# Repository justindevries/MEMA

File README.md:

# MEMA Build Files
An open-source, multiplexed potentiostat kit for at-home diagnostic testing, to be used in tandem with a custom microfluidic assay

This repository contains files for the hardware and firmware required to fabricate, assemble, and initialize the potentiostat.

For source code for complementary iOS app, please see [here](https://github.com/juliamstrauss/NFluidEX-iOS).

For source code for complementary Android app, please see [here](https://github.com/juliamstrauss/NFluidEX-Android).

MEMA is based on ABE-Stat, an open-source potentiostat designed by Jenkins et al. in 2019. Their open-source publication can be accessed [here](https://iopscience.iop.org/article/10.1149/2.0061909jes) for extensive documentation on the basis of its functionality.

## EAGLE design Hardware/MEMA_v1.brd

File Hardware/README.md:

# MEMA Hardware
Design and assembly files for manufacturing of the potentiostat's PCB and 3D-printed housing unit

For Arduino firmware files, please see [here](https://github.com/justindevries/NFluidEX/tree/main/Arduino).

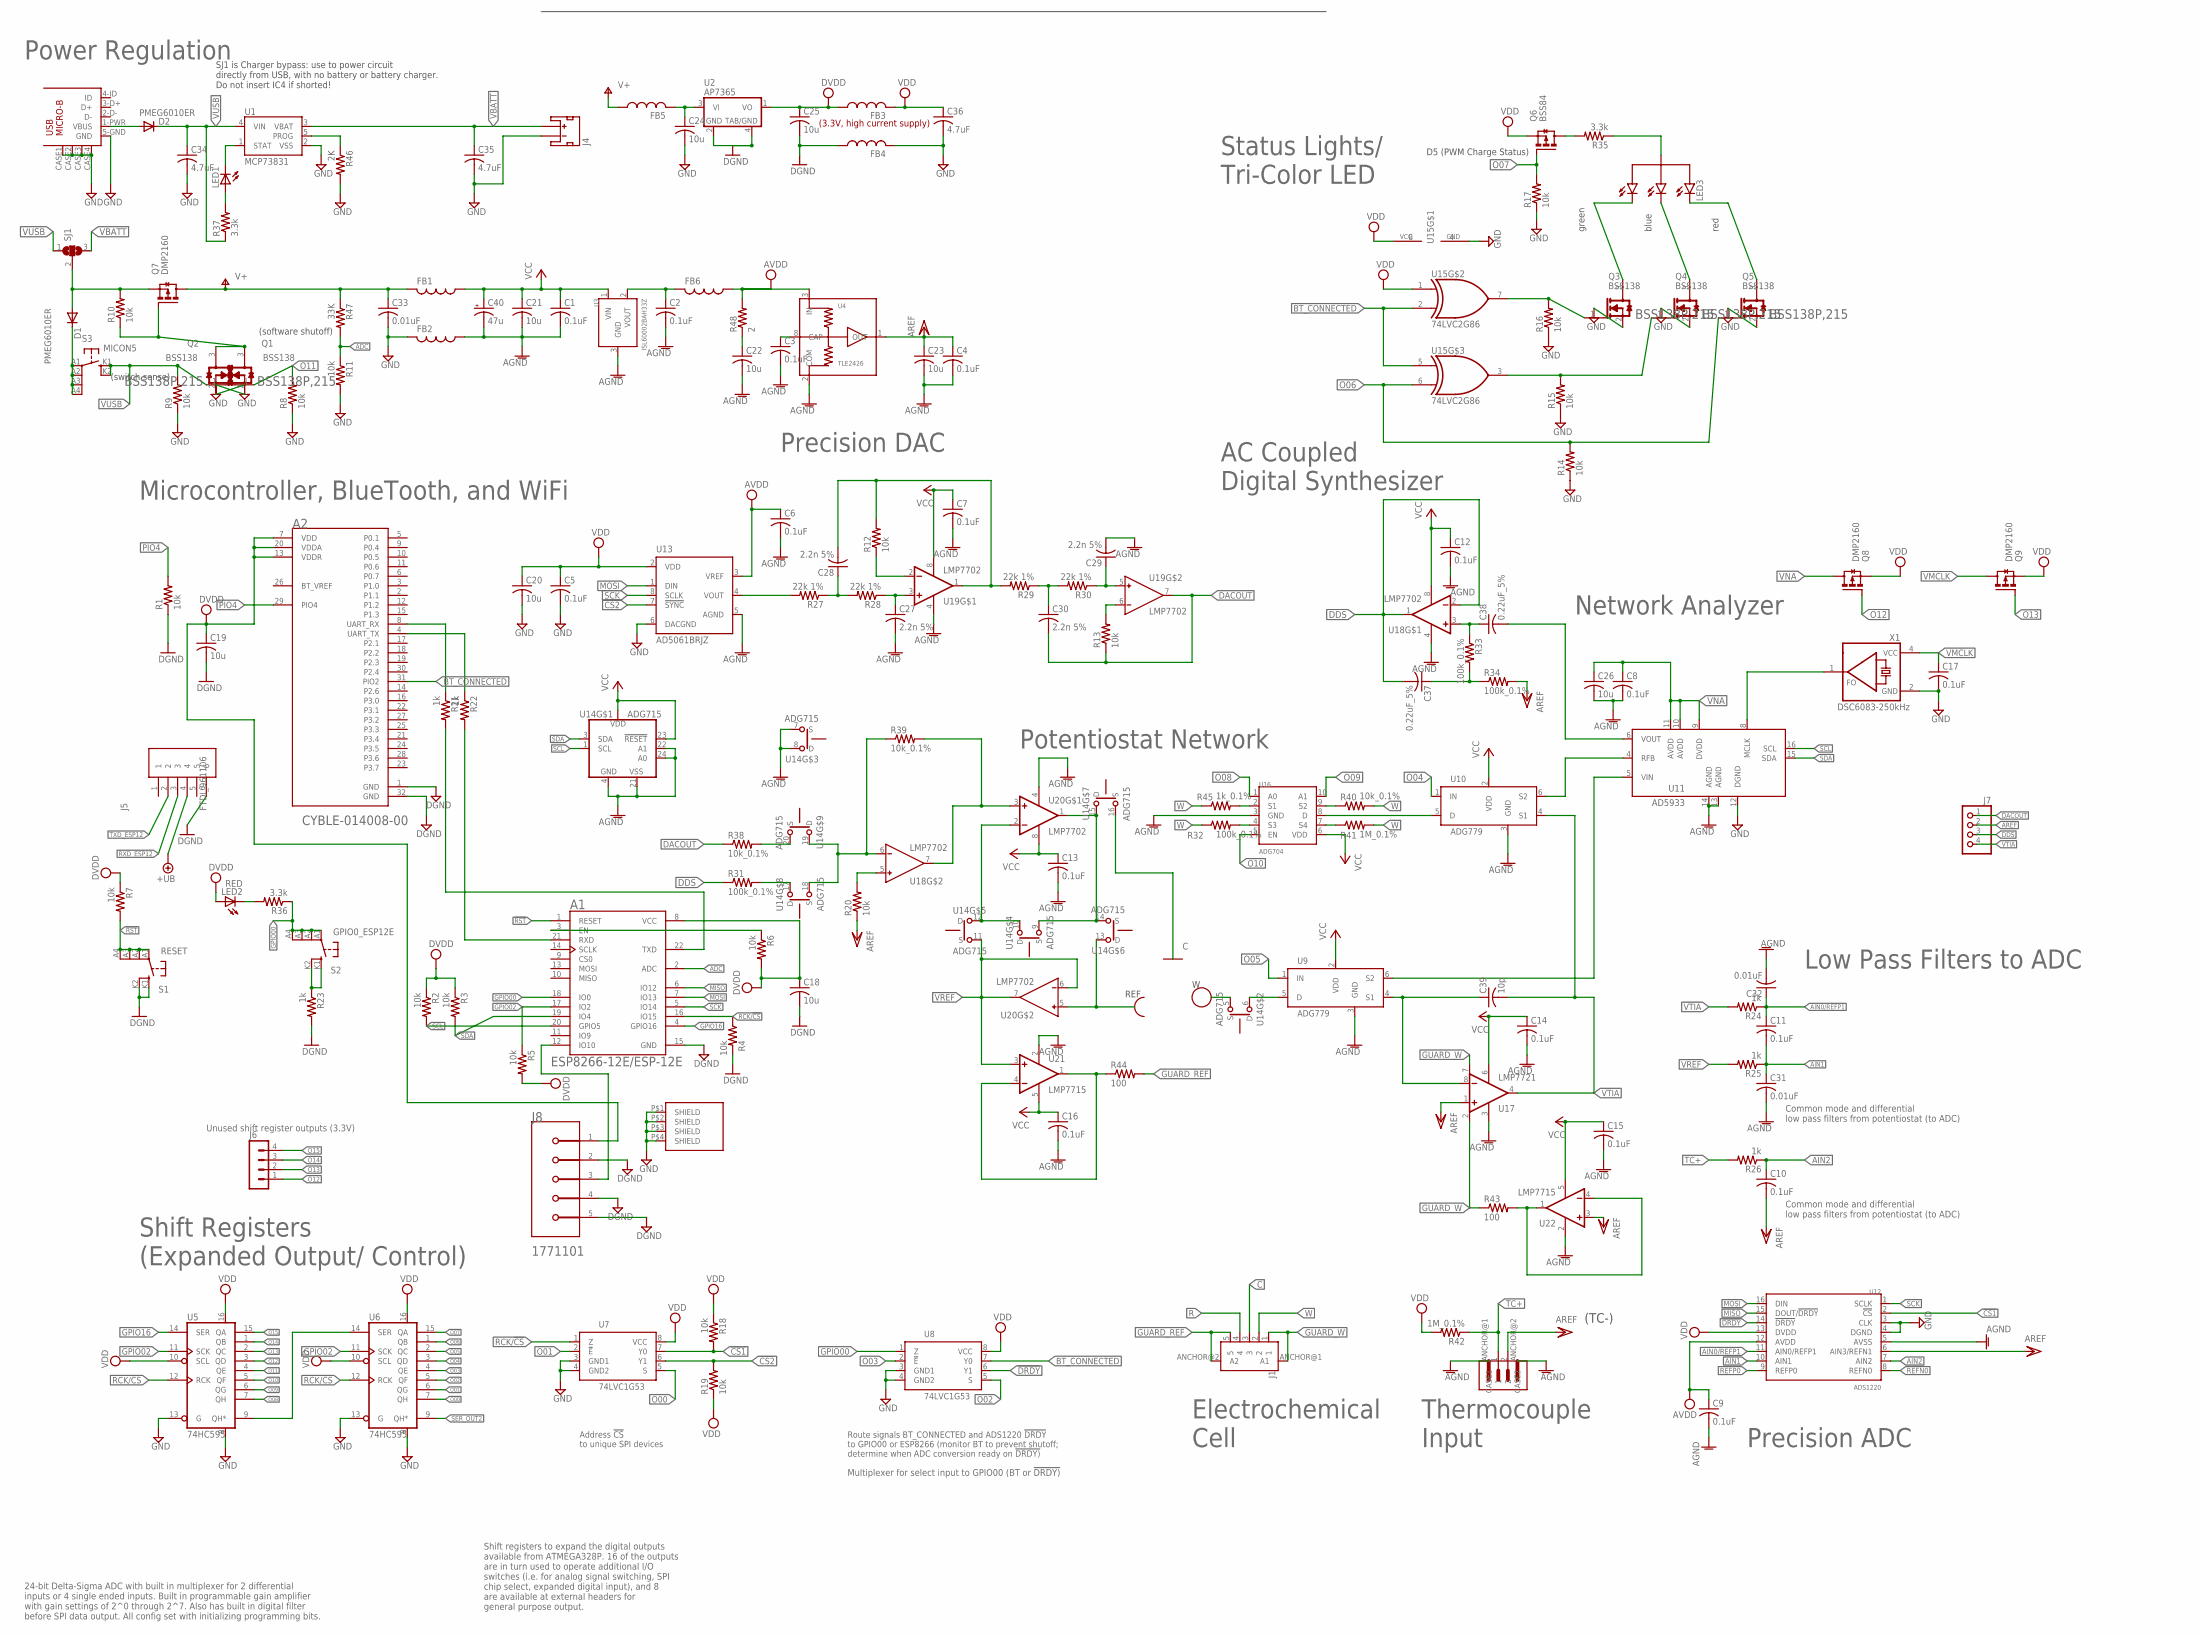
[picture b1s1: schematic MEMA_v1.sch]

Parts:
A1: ESP8266-12E/ESP-12E; XCVR_ESP8266-12E/ESP-12E
A2: CYPRESS_SEMICONDUCTOR_CYBLE-014008-00CYPRESS_SEMI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; CYPRESS_SEMICONDUCTOR_CYBLE-014008-00_0
C1, C2, C3, C4, C5, C6, C7, C8, C9, C10, C11, C12, C13, C14, C15, C16, C17: 0.1uF; C0805
C18, C19, C20, C21, C22, C23, C24, C25, C26: 10u; C0805
C27, C28, C29, C30: 2.2n 5%; C0805
C31, C32, C33: 0.01uF; C0805
C34, C35, C36: 4.7uF; C0805
C37, C38: 0.22uF_5%; C0805
C39: 10p; C0805
C40: 47u; D/7343-31W
D1, D2: PMEG6010ER; DIODE_SOD123
FB1, FB2, FB3, FB4, FB5, FB6: FERRITE_BEAD_5A_0805; R0805
J1: 5-PIN-VERTICAL-PHOENIX_2.5MM-SMD; 5-PIN-VERT_PHOENIX_SMD
J2: 1A_JENKINS_2013_2PIN_SMD_PHOENIX_CONTACTVERTICAL; 2-PIN-VERT_PHOENIX_SMD
J3: USB-MICRO-B; USB_MICRO_B_WURTH_629105136821
J4: JST_2MM_MALE; JST-2-SMD
J5: FTDI_961106; TSM-106-XX-XXX-SV
J6: MA04-1
J7: PINHD-1X4; 1X04
J8: PHOENIX_CONTACT_1771101PHOENIX_CONTACT_1771101_0_0; PHOENIX_CONTACT_1771101_0
LED1: LEDCHIPLED_1206; CHIPLED_1206
LED2: RED; LED-1206
LED3: LED_RBG_COM_ANODE; LED_RGB_WURTH_150141M173100
Q1, Q2, Q3, Q4, Q5: BSS138; NEXPERIA_BSS138P_215_0
Q6: BSS84; SOT-23-3
Q7, Q8, Q9: DMP2160; SOT-23-3
R1, R2, R3, R4, R5, R6, R7, R8, R9, R10, R11, R12, R13, R14, R15, R16, R17, R18, R19, R20: 10k; R0805
R21, R22, R23, R24, R25, R26: 1k; R0805
R27, R28, R29, R30: 22k 1%; R0805
R31, R32, R33, R34: 100k_0.1%; R0805
R35, R36, R37: 3.3k; R0805
R38, R39, R40: 10k_0.1%; R0805
R41, R42: 1M_0.1%; R0805
R43, R44: 100; R0805
R45: 1k_0.1%; R0805
R46: 2K; R0805
R47: 33K; R0805
R48: 2; R2512
S1: RESET; RAFI-MICON5_SWITCH
S2: GPIO0_ESP12E; RAFI-MICON5_SWITCH
S3: MICON5; RAFI-MICON5_SWITCH
SH1: SMARTDART_SHIELD; SMARTDART-SHIELD
SJ1: SJ2W; SJ_2
U1: MCP73831; SOT23-5
U2: AP7365; SOT-223
U3: ISL60002BAH33Z; SOT-23-3
U4: TLE2426; SOIC-8
U5, U6: 74HC595; TSSOP16
U7, U8: 74LVC1G53; VSSOP8
U9, U10: ADG779; SC70-6
U11: AD5933; SSOP-16
U12: ADS1220; TSSOP16
U13: AD5061BRJZ; SOT-23-8
U14: ADG715; TSSOP24
U15: 74LVC2G86; US-8
U16: ADG704; MSOP10
U17: LMP7721; SOIC-8
U18, U19: LMP7702; UMAX8
U20: LMP7702; MSOP8
U21, U22: LMP7715; SOT23-5
X1: DSC6083-250kHz; DSC60XX_OSCILLATOR_3.2X2.5MM

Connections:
!CS1: R18.2, U7.7 (Y0), U12.2 (!CS)
!CS2: R19.2, U7.6 (Y1), U13.7 (!SYNC)
!DRDY: U8.6 (Y1), U12.14 (!DRDY)
!RST: A1.1 (RESET), R7.2, S1.A1, S1.A2 (P1), S1.A3 (P2), S1.A4 (P3)
+UB: J5.4
AD5933_VIN: U9.6 (S2), U11.5 (VIN)
ADC: A1.2 (ADC), R11.1, R47.2
AGND: C1.2, C2.2, C3.2, C4.2, C6.2, C7.2, C8.2, C9.2, C12.2, C13.2, C14.2, C15.2, C16.2, C21.2, C22.2, C23.2, C26.2, C27.2, C29.2, C31.2, C32.2, C40.-, FB2.1, J2.ANCHOR@1 (CASE1), J2.ANCHOR@2 (CASE2), U3.3 (GND), U4.2 (COM), U9.3 (GND), U10.3 (GND), U11.13 (AGND), U11.14 (AGND), U12.5 (AVSS), U13.5 (AGND), U14.4 (GND), U14.7 (S), U14.8 (D), U14.21 (VSS), U14.22 (A1), U14.24 (A0), U16.3 (GND), U17.3 (V-), U18.4 (V-), U19.4 (V-), U20.4 (V-), U21.2 (V-), U22.2 (V-)
AIN0/REFP1: C11.1, C32.1, R24.1, U12.11 (AIN0/REFP1)
AIN1: C11.2, C31.1, R25.1, U12.10 (AIN1)
AIN2: C10.1, R26.1, U12.7 (AIN2)
AREF: C4.1, C10.2, C23.1, J2.2, J7.2, R20.1, R34.2, U4.1 (OUT), U12.6 (AIN3/REFN1), U17.1 (+IN), U22.3 (+IN)
AVDD: C6.1, C9.1, FB6.1, R48.2, U4.3 (IN), U12.12 (AVDD), U13.3 (VREF)
BT_CONNECTED: A2.31 (PIO2), U8.7 (Y0), U15.2 (I1), U15.5 (I0)
BT_VREF: A2.26 (BT_VREF)
C: J1.3, U14.16 (S)
DACOUT: C30.2, J7.1, R13.1, R38.1, U19.7 (OUT)
DDS: C37.2, J7.3, R31.1, U18.1 (OUT), U18.2 (-IN)
DGND: A1.15 (GND), A2.1 (GND), A2.32 (GND), C18.2, C19.2, C25.2, FB4.1, J5.6, J8.2, J8.4 (MNT_1), J8.5 (MNT_2), R1.1, R4.2, R23.2, S1.K1 (S), S1.K2 (S1), U2.2 (GND), U2.4 (GND1)
DVDD: A1.8 (VCC), A2.7 (VDD), A2.13 (VDDR), A2.20 (VDDA), C18.1, C19.1, C25.1, FB3.1, J8.1, LED2.A, R2.1, R3.1, R5.2, R6.2, R7.1, U2.1 (VO)
GND: C5.2, C17.2, C20.2, C24.2, C33.2, C34.2, C35.2, C36.2, FB2.2, FB4.2, J3.5-GND (GND), J3.CASE1 (CASE), J3.CASE2 (CASE), J3.CASE3 (CASE), J3.CASE4 (CASE), J4.1 (-), Q1.2 (S), Q2.2 (S), Q3.2 (S), Q4.2 (S), Q5.2 (S), R8.1, R9.1, R11.2, R14.1, R15.1, R16.1, R17.1, R46.2, SH1.P$1, SH1.P$2, SH1.P$3, SH1.P$4, U1.2 (VSS), U5.8 (GND), U5.13 (G), U6.8 (GND), U6.13 (G), U7.3 (GND1), U7.4 (GND2), U8.3 (GND1), U8.4 (GND2), U11.12 (DGND), U12.3 (CLK), U12.4 (DGND), U13.6 (DACGND), U15.4 (GND), X1.2 (GND)
GPIO00: A1.18 (IO0), R36.1, S2.A1, S2.A2 (P1), S2.A3 (P2), S2.A4 (P3), U8.1 (Z)
GPIO02: A1.17 (IO2), R5.1, U5.11 (SCK), U6.11 (SCK)
GPIO10: A1.12 (IO10), J8.3
GPIO16: A1.4 (GPIO16), U5.14 (SER)
GUARD_REF: J1.5, J1.ANCHOR@2 (A2), R44.2
GUARD_W: J1.1, J1.ANCHOR@1 (A1), R43.1, U17.2 (GUARD), U17.7 (GUARD)
MISO: A1.6 (IO12), U12.15 (DOUT/!DRDY)
MOSI: A1.7 (IO13), U12.16 (DIN), U13.1 (DIN)
unnamed: A2.8 (UART_RX), R21.1
unnamed: U14.10 (D), U14.12 (D), U20.2 (-IN)
unnamed: D2.A, J3.1-PWR (VBUS)
unnamed: A2.4 (UART_TX), R22.1
unnamed: Q3.1 (G), R16.2, U15.7 (O)
unnamed: U9.5 (D), U14.6 (D)
unnamed: R46.1, U1.5 (PROG)
unnamed: U5.9 (QH*), U6.14 (SER)
unnamed: C27.1, R28.1, U19.3 (+IN)
unnamed: LED1.C, U1.1 (STAT)
unnamed: R27.2, U13.4 (VOUT)
unnamed: LED1.A, R37.2
unnamed: C22.1, R48.1
unnamed: R31.2, U14.17 (D)
unnamed: C28.1, R27.1, R28.2
unnamed: R23.1, S2.K1 (S), S2.K2 (S1)
unnamed: Q4.1 (G), R15.2, U15.3 (O)
unnamed: D1.C, S3.A1, S3.A2 (P1), S3.A3 (P2), S3.A4 (P3)
unnamed: C3.1, U4.8 (CAP)
unnamed: C28.2, R12.2, R29.2, U19.1 (OUT)
unnamed: C30.1, R29.1, R30.2
unnamed: C29.1, R30.1, U19.5 (IN+)
unnamed: R12.1, U19.2 (-IN)
unnamed: U14.9 (S), U14.14 (S), U14.15 (D), U20.1 (OUT)
unnamed: R13.2, U19.6 (IN-)
unnamed: LED2.C, R36.2
unnamed: C2.1, FB6.2, U3.2 (VOUT)
unnamed: C39.1, U9.4 (S1), U17.8 (-IN)
unnamed: R39.1, U14.18 (S), U14.19 (D), U18.6 (IN-)
unnamed: R39.2, U18.7 (OUT), U20.3 (+IN)
unnamed: U10.6 (S2), U11.4 (RFB)
unnamed: R41.1, U16.7 (S4)
unnamed: R44.1, U21.1 (OUT), U21.4 (-IN)
unnamed: R40.1, U16.9 (S2)
unnamed: Q1.3 (D), Q2.3 (D), Q7.1 (G), R10.1
unnamed: U10.5 (D), U16.8 (D)
unnamed: R45.2, U16.2 (S1)
unnamed: R32.2, U16.4 (S3)
unnamed: LED3.G, Q3.3 (D)
unnamed: R43.2, U22.1 (OUT), U22.4 (-IN)
unnamed: LED3.B, Q4.3 (D)
unnamed: LED3.R, Q5.3 (D)
unnamed: Q6.3 (D), R35.2
unnamed: LED3.A, R35.1
unnamed: R38.2, U14.20 (S)
unnamed: C24.1, FB5.2, U2.3 (VI)
unnamed: A1.3 (EN), R6.1
unnamed: U11.8 (MCLK), X1.1 (FO)
unnamed: D1.A, Q7.2 (S), R10.2, SJ1.2
unnamed: R20.2, U18.5 (IN+)
unnamed: C37.1, R33.2, R34.1
unnamed: C38.1, R33.1, U18.3 (+IN)
unnamed: C38.2, U11.6 (VOUT)
O00: U6.7 (QH), U7.5 (S)
O01: U6.6 (QG), U7.2 (!E)
O02: U6.5 (QF), U8.5 (S)
O03: U6.4 (QE), U8.2 (!E)
O04: U6.3 (QD), U10.1 (IN)
O05: U6.2 (QC), U9.1 (IN)
O06: Q5.1 (G), R14.2, U6.1 (QB), U15.6 (I1)
O07: Q6.1 (G), R17.2, U6.15 (QA)
O08: U5.7 (QH), U16.1 (A0)
O09: U5.6 (QG), U16.10 (A1)
O10: U5.5 (QF), U16.5 (EN)
O11: Q1.1 (G), R8.2, U5.4 (QE)
O12: J6.1, Q8.1 (G), U5.3 (QD)
O13: J6.2, Q9.1 (G), U5.2 (QC)
O14: J6.3, U5.1 (QB)
O15: J6.4, U5.15 (QA)
PIO4: A2.29 (PIO4), R1.2
R: J1.4, U14.13 (D), U20.5 (IN+)
RCK/!CS: A1.16 (IO15), R4.1, U5.12 (RCK), U6.12 (RCK), U7.1 (Z)
REFN0: U12.8 (REFN0)
REFP0: U12.9 (REFP0)
RXD_ESP12: A1.21 (RXD), J5.3, R22.2
SCK: A1.5 (IO14), U12.1 (SCLK), U13.8 (SCLK)
SCL: A1.20 (GPIO5), R2.2, U11.16 (SCL), U14.1 (SCL)
SDA: A1.19 (IO4), R3.2, U11.15 (SDA), U14.3 (SDA)
SER_OUT2: U6.9 (QH*)
TC+: J2.1, R26.2, R42.1
TXD_ESP12: A1.22 (TXD), J5.2, R21.2
V+: C33.1, FB1.2, FB5.1, Q7.3 (D), R47.1
VBATT: C35.1, J4.2 (+), SJ1.3, U1.3 (VBAT)
VCC: C1.1, C7.1, C12.1, C13.1, C14.1, C15.1, C16.1, C21.1, C40.+, FB1.1, U3.1 (VIN), U9.2 (VDD), U10.2 (VDD), U14.2 (VDD), U14.23 (!RESET), U16.6 (VDD), U17.6 (V+), U18.8 (V+), U19.8 (V+), U20.8 (V+), U21.5 (V+), U22.5 (V+)
VDD: C5.1, C20.1, C36.1, FB3.2, Q6.2 (S), Q8.2 (S), Q9.2 (S), R18.1, R19.1, R42.2, U5.10 (SCL), U5.16 (VCC), U6.10 (SCL), U6.16 (VCC), U7.8 (VCC), U8.8 (VCC), U12.13 (DVDD), U13.2 (VDD), U15.1 (I0), U15.8 (VCC)
VMCLK: C17.1, Q9.3 (D), X1.4 (VCC)
VNA: C8.1, C26.1, Q8.3 (D), U11.9 (DVDD), U11.10 (AVDD), U11.11 (AVDD)
VREF: R25.2, U14.11 (S), U20.6 (IN-), U20.7 (OUT), U21.3 (+IN)
VTIA: C39.2, J7.4, R24.2, U10.4 (S1), U17.4 (OUT)
VUSB: C34.1, D2.C, Q2.1 (G), R9.2, R37.1, S3.K1 (S), S3.K2 (S1), SJ1.1, U1.4 (VIN)
W: J1.2, R32.1, R40.2, R41.2, R45.1, U14.5 (S)

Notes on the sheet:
(3.3V, high current supply)
Route signals BT_CONNECTED and ADS1220 !DRDY to GPIO00 or ESP8266 (monitor BT to prevent shutoff; determine when ADC conversion ready on !DRDY)
Shift registers to expand the digital outputs available from ATMEGA328P. 16 of the outputs are in turn used to operate additional I/O switches (i.e. for analog signal switching, SPI chip select, expanded digital input), and 8 are available at external headers for general purpose output.
Multiplexer for select input to GPIO00 (BT or !DRDY)
Power Regulation
Microcontroller, BlueTooth, and WiFi
Precision ADC
Shift Registers (Expanded Output/ Control)
24-bit Delta-Sigma ADC with built in multiplexer for 2 differential inputs or 4 single ended inputs. Built in programmable gain amplifier with gain settings of 2^0 through 2^7. Also has built in digital filter before SPI data output. All config set with initializing programming bits.
Common mode and differential low pass filters from potentiostat (to ADC)
Address !CS to unique SPI devices
(switch sense)
(software shutoff)
Precision DAC
Network Analyzer
Potentiostat Network
Low Pass Filters to ADC
Thermocouple Input
Electrochemical Cell
D5 (PWM Charge Status)
green
blue
red
Status Lights/ Tri-Color LED
(TC-)
Unused shift register outputs (3.3V)
REF
SJ1 is Charger bypass: use to power circuit directly from USB, with no battery or battery charger. Do not insert IC4 if shorted!
AC Coupled Digital Synthesizer

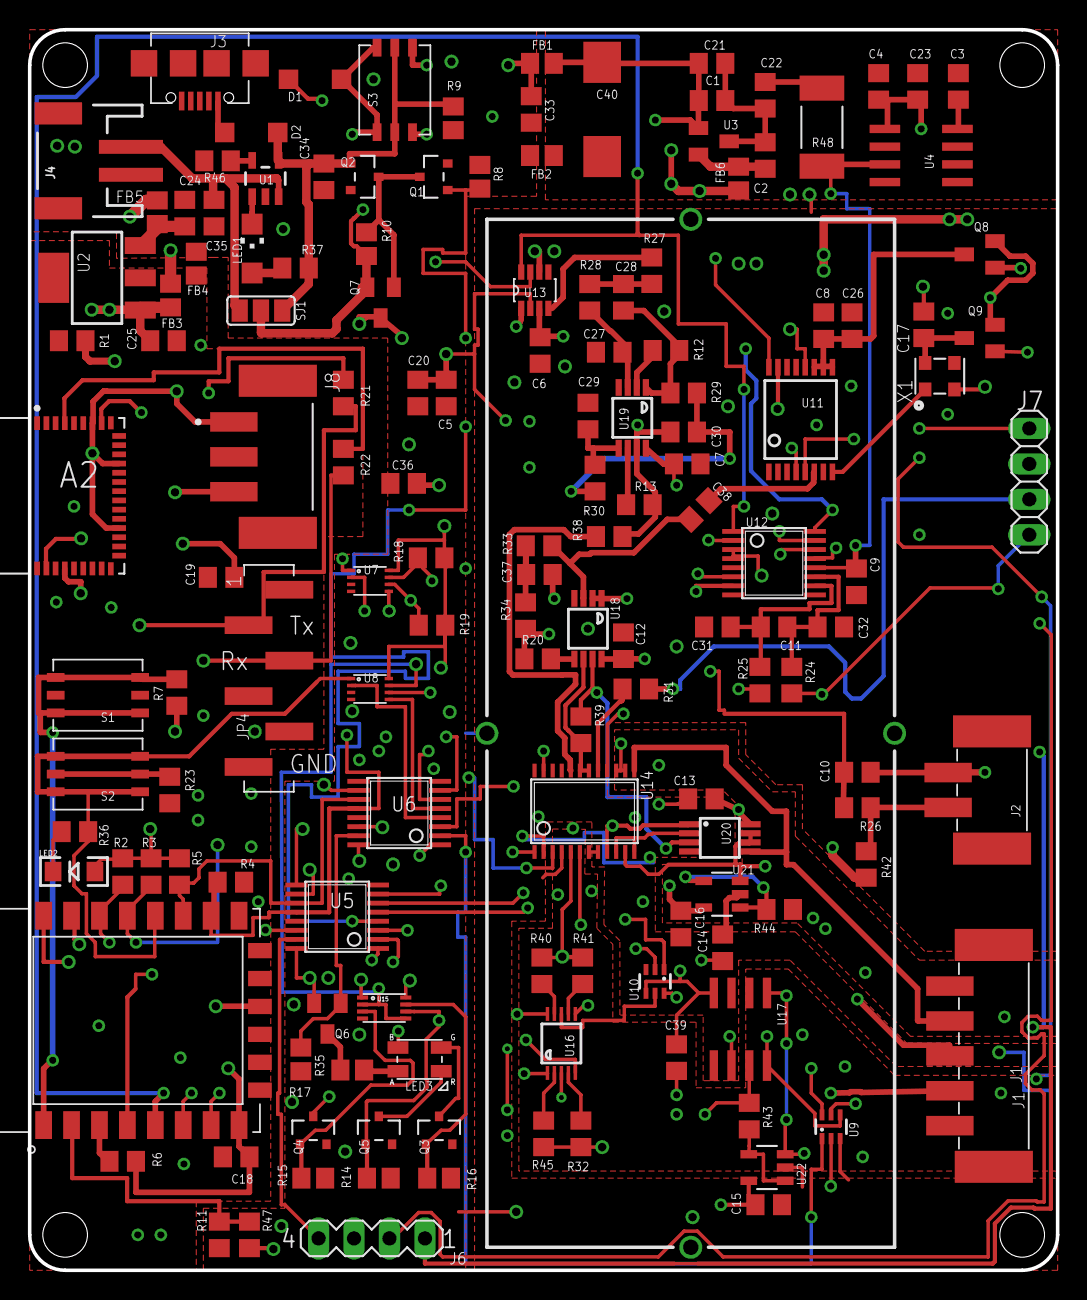
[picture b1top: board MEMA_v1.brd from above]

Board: 4 copper layers, 73.7 x 88.9 mm, 146 parts (0 on the bottom side), 115 nets.

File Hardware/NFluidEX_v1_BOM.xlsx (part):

| Bill of Materials for pc board: "NFluidEX_v1" as of: 17/3/2022 1:44 PM
Ref | Item | Quantity | for 50 | w overage | Designator | Mfctr. Part Number | Description | Value | Package | Type | Manufacturer | Distributor | Dstbr. Part #
PSTAT1 | 1 | 1 | 50 | 150 | A1 | ESP-12F | ESP8266 WiFi Module |  |  |  | Adafruit Industries | Digikey | 1528-1438-ND
PSTAT2 | 2 | 1 | 50 | 150 | A2 | CYBLE-014008-00 | RX TXRX MODULE BT TRC ANT SMD |  |  | smt | Cypress Semiconductor Corp | Digikey | 428-3600-1-ND
PSTAT3 | 3 | 17 | 850 | 950 | C1 - C17 | C0805C104K3RACTU | CAP CER 0.1UF 25V 10% X7R 0805 | 0.1 uF | 0805 | smt | Kemet | Digikey | 399-1168-1-ND
PSTAT4 | 4 | 9 | 450 | 550 | C18 - C26 | C2012X5R1C106M085AC | CAP CER 10UF 16V 20% X5R 0805 | 10 uF | 0805 | smt | TDK Corporation | Digikey | 445-7645-2-ND
PSTAT5 | 5 | 4 | 200 | 300 | C27 - C30 | C0805C222K5RACTU | CAP CER 2200PF 50V X7R 0805 | 2200pF | 0806 | smt | KEMET | Digikey | 399-1151-1-ND
PSTAT6 | 6 | 3 | 150 | 250 | C31 - C33 | 08055C103KAT2A | CAP CER 10000PF 50V 10% X7R 0805 | 10000 pF | 0805 | smt | AVX Corporation | Digikey | 478-1383-1-ND
PSTAT7 | 7 | 3 | 150 | 250 | C34 - C36 | GRM219R61E475KA73D | CAP CER 4.7UF 25V X5R 0805 | 4.7 uF | 0805 | smt | Murata Electronics North America | Digikey | 490-12753-1-ND
PSTAT8 | 8 | 2 | 100 | 200 | C37, C38 | CC0805JRX7R7BB224 | CAP CER 0.22UF 16V X7R 0805 | 0.22 uF | 0805 | smt | Yageo | Digikey | 311-4267-1-ND
PSTAT9 | 9 | 1 | 50 | 150 | C39 | 08055A100FAT2A | CAP CER 10PF 50V 1% NP0 0805 | 10 pF | 0805 | smt | AVX Corporation | Digikey | 478-10493-1-ND
PSTAT10 | 10 | 1 | 50 | 150 | C40 | EEF-CD0J470R | CAP ALUM POLY 47UF 20% 6.3V SMD | 47 uF | 7343 | smt | Panasonic Electronic Components | Digikey | PCE3160CT-ND
PSTAT11 | 11 | 2 | 100 | 200 | D1, D2 | PMEG6010ER,115 | DIODE SCHOTTKY 60V 1A SOD123W |  | SOD123W | smt | Nexperia USA Inc. | Digikey | 1727-5846-1-ND
PSTAT12 | 12 | 6 | 300 | 400 | FB1 - FB6 | 742792097 | FERRITE BEAD 1.5 KOHM 0805 1LN |  | 0805 | smt | Wurth Electronics Inc. | Digikey | 732-4649-1-ND
PSTAT13 | 13 | 1 | 50 | 60 | J1 | 1771127 | CONN TERM BLK 5POS 2.5MM SMD |  |  | smt | Phoenix Contact | Digikey | 277-2075-1-ND
PSTAT14 | 14 | 1 | 50 | 60 | J2 | 1771091 | CONN TERM BLK 2POS 2.5MM SMD |  |  | smt | Phoenix Contact | Digikey | 277-2072-1-ND
PSTAT15 | 15 | 1 | 50 | 60 | J3 | 629105136821 | CONN RCPT USB MICRO B R/A SMT |  |  | smt | Wurth Electronics Inc. | Digikey | 732-3155-1-ND
PSTAT16 | 16 | 1 | 50 | 60 | J4 | S2B-PH-SM4-TB(LF)(SN) | CONN HEADER PH SIDE 2POS 2MM SMD |  |  | smt | JST Sales America Inc. | Digikey | 455-1749-1-ND
PSTAT17 | 17 | 1 | 50 | 60 | J5 | 961106-6300-AR-PR | CONN HEADER VERT 6POS GOLD SMD |  |  | smt | 3M | Digikey | 3M9488CT-ND
PSTAT18 | 18 | 1 | 50 | 60 | J8 | 1771101 | TERM BLK 3P TOP ENTRY 2.5MM SMD |  |  | smt | Phoenix Contact | Digikey | 277-2073-1-ND
PSTAT19 | 19 | 2 | 100 | 120 | LED1, LED2 | QBLP651-R | LED RED CLEAR 1206 SMD |  | 1206 | smt | QT Brightek (QTB) | Digikey | 1516-1172-1-ND
PSTAT20 | 20 | 1 | 50 | 60 | LED3 | 150141M173100 | LED RGB CLEAR 1411 SMD |  |  | smt | Wurth Electronics Inc | DigiKey | 732-4998-1-ND
PSTAT21 | 21 | 5 | 250 | 275 | Q1 - Q5 | BSS138 | MOSFET N-CH 50V 220MA SOT-23 |  | SOT-23-3 | smt | Fairchild Semiconductor | Digikey | BSS138CT-ND
PSTAT22 | 22 | 1 | 50 | 75 | Q6 | BSS84 | MOSFET P-CH 50V 130MA SOT-23 |  | SOT-23-3 | smt | Fairchild Semiconductor | Digikey | BSS84CT-ND
PSTAT23 | 23 | 3 | 150 | 175 | Q7 - Q9 | DMP2160UW-7 | MOSFET P-CH 20V 1.5A SOT-323 |  |  |  | Diodes Incorporated | Digikey | DMP2160UWDICT-ND
PSTAT24 | 24 | 20 | 1000 | 1100 | R1 - R20 | ERJ-P06J103V | RES 10K OHM 1/2W 5% 0805 SMD | 10 k | 0805 | smt | Panasonic Electronic Components | Digikey | P10KADCT-ND
PSTAT25 | 25 | 6 | 300 | 400 | R21 - R26 | ERJ-P06J102V | RES SMD 1K OHM 5% 1/2W 0805 | 1 k | 0805 | smt | Panasonic Electronic Components | Digikey | P1.0KADCT-ND
PSTAT26 | 26 | 4 | 200 | 300 | R27 - R30 | ERJ-6GEYJ223V | RES SMD 22K OHM 5% 1/8W 0805 | 22k | 0805 | smt | Panasonic Electronic Components | Digikey | P22KACT-ND
PSTAT27 | 27 | 4 | 200 | 300 | R31 - R34 | ERA-6APB104V | RES SMD 100K OHM 0.1% 1/8W 0805 | 100k | 0805 | smt | Panasonic Electronic Components | Digikey | P100KAZCT-ND
PSTAT28 | 28 | 3 | 150 | 250 | R35 - R37 | ERJ-P06J332V | RES SMD 3.3K OHM 5% 1/2W 0805 | 3.3k | 0805 | smt | Panasonic Electronic Components | Digikey | P3.3KADCT-ND
PSTAT29 | 29 | 3 | 150 | 250 | R38 - R40 | ERA-6AEB103V | RES SMD 10K OHM 0.1% 1/8W 0805 | 10k | 0805 | smt | Panasonic Electronic Components | Digikey | P10KDACT-ND
PSTAT30 | 30 | 2 | 100 | 200 | R41, R42 | RG2012P-105-B-T5 | RES SMD 1M OHM 0.1% 1/8W 0805 | 1M | 0805 | smt | Panasonic Electronic Components | Digikey | RG20P1.0MBCT-ND
PSTAT31 | 31 | 2 | 100 | 200 | R43, R44 | ERJ-P6WJ101V | RES SMD 100 OHM 5% 1/2W 0805 | 100W | 0805 | smt | Panasonic Electronic Components | Digikey | P16942CT-ND
PSTAT32 | 32 | 1 | 50 | 150 | R45 | ERA-6AEB102V | RES SMD 1K OHM 0.1% 1/8W 0805 | 1k | 0805 | smt | Panasonic Electronic Components | Digikey | P1.0KDACT-ND
PSTAT33 | 33 | 1 | 50 | 150 | R46 | ERJ-P06J202V | RES SMD 2K OHM 5% 1/2W 0805 | 2k | 0805 | smt | Panasonic Electronic Components | Digikey | P2.0KADCT-ND
PSTAT34 | 34 | 1 | 50 | 150 | R47 | ERJ-P06J333V | RES SMD 33K OHM 5% 1/2W 0805 | 33k | 0805 | smt | Panasonic Electronic Components | Digikey | P33KADCT-ND
PSTAT35 | 35 | 1 | 50 | 100 | R48 | ERJ-1TYJ2R0U | RES SMD 2 OHM 5% 1W 2512 | 2W | 2512 | smt | Panasonic Electronic Components | Digikey | PT2.0XCT-ND
PSTAT36 | 36 | 3 | 150 | 160 | S1 - S3 | 1.14002.1110000 | SWITCH PUSH SPST-NO 0.1A 35V |  |  | smt | RAFI USA | Digikey | 1715-1675-1-ND
PSTAT37 | 37 | 1 | 50 | 60 | U1 | MCP73831T-2ACI/OT | IC CONTROLLR LI-ION 4.2V SOT23-5 |  | SOT23-5 | smt | Microchip Technology | Digikey | MCP73831T-2ACI/OTCT-ND
PSTAT38 | 38 | 1 | 50 | 60 | U2 | AP7365-33EG-13 | IC REG LINEAR 3.3V 600MA SOT223 |  | SOT-2233L | smt | Diodes Incorporated | Digikey | AP7365-33EG-13DICT-ND
PSTAT39 | 39 | 1 | 50 | 60 | U3 | ISL60002BAH333Z-T7A | IC VREF SERIES 3.3V SOT23-3 | 3.3V | SOT-23-3 | smt | Intersil | Digikey | ISL60002BAH333Z-T7ACT-ND
PSTAT40 | 40 | 1 | 50 | 60 | U4 | TLE2426IDR | IC VREF GND REF ADJ 8SOIC |  | 8SOIC | smt | Texas Instruments | Digikey | 296-1345-1-ND
PSTAT41 | 41 | 2 | 100 | 110 | U5, U6 | MM74HC595MTCX | IC SHIFT REGISTER 8-BIT 16-TSSOP |  | 16-TSSOP | smt | Fairchild/ON Semiconductor | Digikey | MM74HC595MTCXCT-ND
PSTAT42 | 42 | 2 | 100 | 110 | U7, U8 | 74LVC1G53DC,125 | IC MUX/DEMUX 2X1 8VSSOP |  | 8VSSOP | smt | Nexperia USA Inc. | Digikey | 1727-3492-1-ND
PSTAT43 | 43 | 2 | 100 | 110 | U9, U10 | ADG779BKSZ-REEL7 | IC SWITCH SPDT SC70-6 |  | SC-70-6 | smt | Analog Devices Inc. | Digikey | ADG779BKSZ-REEL7CT-ND
PSTAT44 | 44 | 1 | 50 | 60 | U11 | AD5933YRSZ-REEL7 | NETWORK ANALYZER 12B 1MSP 16SSOP |  | 16SSOP | smt | Analog Devices Inc. | Digikey | AD5933YRSZ-REEL7CT-ND
PSTAT45 | 45 | 1 | 50 | 60 | U12 | ADS1220IPWR | IC ADC 24-BIT 2KSPS 16-TSSOP |  | 16-TSSOP | smt | Analog Devices Inc. | Digikey | 296-39851-1-ND
PSTAT46 | 46 | 1 | 50 | 60 | U13 | AD5061BRJZ-2REEL7 | IC DAC 16BIT SPI/SRL SOT23-8 |  | SOT23-8 | smt | Analog Devices Inc. | Digikey | AD5061BRJZ-2REEL7CT-ND
PSTAT47 | 47 | 1 | 50 | 60 | U14 | ADG715BRUZ | IC SWITCH OCTAL SPST 24TSSOP |  | 24TSSOP | smt | Analog Devices Inc. | Digikey | ADG715BRUZ-ND
PSTAT48 | 48 | 1 | 50 | 60 | U15 | SN74LVC2G86DCUR | IC GATE XOR 2CH 2-INP US8 | XOR | US8 | smt | Texas Instruments | Digikey | 296-13275-1-ND
PSTAT49 | 49 | 1 | 50 | 60 | U16 | ADG704BRMZ | IC MULTIPLEXER 4X1 10USOIC |  | 10USOIC | smt | Analog Devices Inc. | Digikey | ADG704BRMZ-ND
PSTAT50 | 50 | 1 | 50 | 60 | U17 | LMP7721MA/NOPB | IC AMP PREC 3FA BIAS CURR 8SOIC |  | 8SOIC | smt | Texas Instruments | Digikey | LMP7721MA/NOPB-ND
PSTAT51 | 51 | 3 | 150 | 160 | U18 - U20 | LMP7702MM/NOPB | IC OPAMP GP 2.5MHZ RRO 8VSSOP |  | 8-MSOP | smt | Texas Instruments | Digikey | LMP7702MM/NOPBCT-ND
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
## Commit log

2022-09-23 CAM Outputs
2022-09-23 PCB Layout Files
2022-09-23 Housing Unit CAD Files
2023-04-03 Rename NFluidEX.ino to MEMA.ino
2023-04-03 Rename NFluidEX_AnalogFcns.ino to MEMA_AnalogFcns.ino
2023-04-03 Rename NFluidEX_AnalyticalMethods.ino to MEMA_AnalyticalMethods.ino
2023-04-03 Rename NFluidEX_Calibrations.ino to MEMA_Calibrations.ino
2023-04-03 Rename NFluidEX_DigitalConfigurations.ino to MEMA_DigitalConfigurations.ino
2023-04-03 Rename NFluidEX_NetworkAnalyzer.ino to MEMA_NetworkAnalyzer.ino

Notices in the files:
parts and their libraries:
SparkFun-Connectors: Licensing: Creative Commons ShareAlike 4.0 International - https://creativecommons.org/licenses/by-sa/4.0
